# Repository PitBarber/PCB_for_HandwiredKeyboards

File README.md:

# PCB for Handwired Keyboards

### About this repo:
```
Files you can find here are only the kicad project about the PCB design, 
3D design or entire keyboard firmware will be linked in this description.
```

### Why?

This project provides to handwired keyboards a support to have underglow keycaps.
PCBs was designed for keyboard with different form factors, for example: dactyl manuform. Its geometry makes makers hard to desing flexible PCBs, and them could be available only for some kind of dactyl manuform.
These 15mmx15mm PCBs are near to size of a keyboard Switch, so there can be placed in any custom keyboard, if a switch fits, a PCB will do it so, this is suitable for customizable keyboards.
Every PCB was designed with a LED neopixel, 100nF capacitor and a 1n4148 diode.

[3D design used in this project](https://github.com/joseandres42/dactyl-manuform-mini-keyboard) - 5x6 dactyl manuform 3D design por 3D printing by @joseandres42

In case you want to use the same design, @joseandres42 has a spanish dvorak layout
for this version of dactyl manuform [right in this forked repo](https://github.com/joseandres42/qmk_firmware/tree/master/keyboards/handwired/dactyl_manuform/5x6/keymaps/joseandres42)  

### The PCB 

Handsoldering entire PCB is possible and i did it with the 62 PCBs.

Top of the PCB only has the builtin SK6812 4020 neopixel, they can be mounted sized or faceup. Footprint isn't in kicad's official libraries ( a merge will be done).

Bottom has a 100nF capacitor, necesary for the neopixel, a 1n4148 diode, for ROW to COL wiring ( remember it for the QMK config) and finally, the connection pads:
* VCC: 3.3-5v high level voltage node.
* DIN: Data In of the neopixel.
* DOUT: Data Out of the neopixel.
* GND: Ground node.
* COL: Column node.
* ROW: Row node.

### PCB TECHNICAL INFORMATION:

I will show you some technical data about boad sizes and LED SK6812 footprint:

Here you can see the size of the pcb, distance between pads and pads size.

Now, important information about SK6812 footprint, pads and sizes:

This information is directly collected from official [SK6812 SIDE 4020 datasheet](http://www.normandled.com/upload/201804/SK6812%204020%20SIDE%20LED%20Datasheet.pdf)

Footprint was designed using the FootPrint editing Tool provided by Kicad.

### Wiring
COL wiring:

ROW wiring:

This is the wiring in the lefthand keyboard, the righthand will be the same, but mirrored.

* Boards Used: Arduino Pro micro in both cases
* [Oficial Dactyl Manuform](https://github.com/abstracthat/dactyl-manuform) - More wiring tips by @abstracthat

About the neopixel wiring, every DOUT is connected to de next DIN PCB node.

Be carefull with VCC and GND propagation, dont do it lineal, i mean, you can connect VCC and GND eachother, no matters the order.
But if you only have one connection to VCC at start and VCC propagates linear througt PCB it will experiment a fall of ~0.3V
that will cause some fliker due to less voltage feeding.

Best light brightness is between 80-110/255 when you config the lights in QMK.

[QMK neopixel documentation](https://github.com/qmk/qmk_firmware/blob/master/docs/feature_rgblight.md)- Neopixel animations and configuration tips

#### Config Example
```
#define DIODE_DIRECTION COL2ROW

// WS2812 RGB LED strip input and number of LEDs
#define	RGB_DI_PIN F4
#define	RGBLED_NUM 31

/* number of backlight levels */
#define RGBLIGHT_LIMIT_VAL 100
#define BACKLIGHT_LEVELS 3
```
More information at the provided link before.

### Firmware:

[QMK Firmware](https://github.com/qmk/qmk_firmware) - keyboard firmware based on the tmk_keyboard firmware

### Final Results:

### Videos: 
Final result + ASMR siwtch video.

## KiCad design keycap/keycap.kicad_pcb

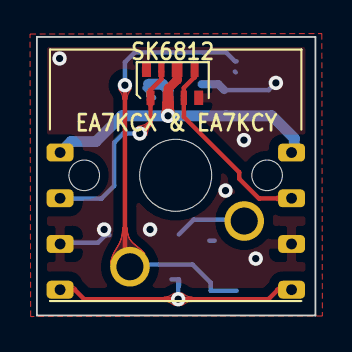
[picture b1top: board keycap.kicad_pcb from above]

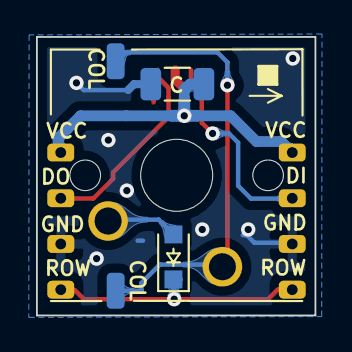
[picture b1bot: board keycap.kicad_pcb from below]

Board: 2 copper layers, 15.5 x 15.5 mm, 13 parts (12 on the bottom side), 5 nets.

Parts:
C: 0.1uF; C_1206_3216Metric
D: 1N4148; D_SOD-323_HandSoldering
J1, J2, J3, J4, J5, J6, J7, J8, J9, J10: Conn_01x01_Female; SolderWirePad_1x01_SMD_1x2mm
SW1: SW_Push_Open; SW_Cherry_MX_1.00u_PCB

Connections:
/COL: J8.1, J9.1, SW1.1
/ROW: D.1, J7.1, J10.1
/VCC: C.1, J1.1, J4.1
GND: C.2, J3.1, J6.1
unnamed: D.2, SW1.2

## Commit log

2021-05-20 Added images & BOM
2021-05-25 images
2021-05-26 PCB technical information
2021-05-26 Soldered PCBs
2021-05-26 Soldered PCBs edit
2021-05-27 Added artistic photo
2021-05-27 deleted some files
2021-08-13 Nueva rama develop
2021-08-14 add images
2021-08-14 add gerber files zip
